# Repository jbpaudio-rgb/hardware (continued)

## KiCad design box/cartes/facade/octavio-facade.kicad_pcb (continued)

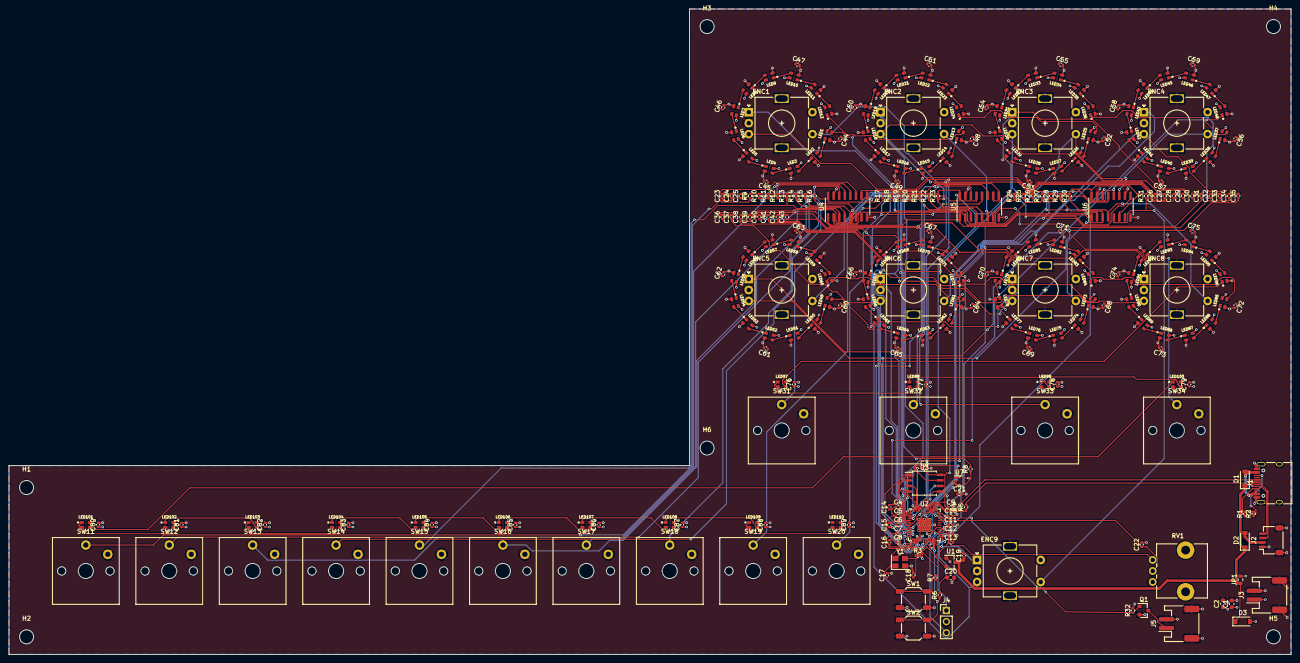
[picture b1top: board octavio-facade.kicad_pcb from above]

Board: 4 copper layers, 292.0 x 147.0 mm, 281 parts (0 on the bottom side), 187 nets.

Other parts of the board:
H1, H2, H3, H4, H5, H6: M3; MountingHole_3.2mm_M3

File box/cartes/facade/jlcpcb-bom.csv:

Comment,Designator,Footprint,LCSC Part #
TYPE-C-31-M-12,J1,USB_C_Receptacle_HRO_TYPE-C-31-M-12,C165948
5.1k,"R1,R2",R_0402_1005Metric,C25905
B5819W,"D1,D2,D3",D_SOD-123,C8598
SM04B-SRSS-TB,J2,JST_SH_SM04B-SRSS-TB_1x04-1MP_P1.00mm_Horizontal,C160404
S2B-PH-SM4-TB,"J3,J5",JST_PH_S2B-PH-SM4-TB_1x02-1MP_P2.00mm_Horizontal,C295747
10uF,"C1,C2,C20",C_0603_1608Metric,C19702
2N7002,Q1,SOT-23,C8545
100k,R32,R_0402_1005Metric,C25741
RP2040,U2,RP2040-QFN-56,C2040
W25Q16JVSSIQ,U3,SOIC-8_5.23x5.23mm_P1.27mm,C131025
100nF,"C3,C4,C5,C6,C7,C8,C9,C10,C11,C12,C13,C16,C21,C22,C23,C24,C25,C44,C45,C46,C47,C48,C49,C50,C51,C52,C53,C54,C55,C56,C57,C58,C59,C60,C61,C62,C63,C64,C65,C66,C67,C68,C69,C70,C71,C72,C73,C74,C75,C76,C77,C78,C79,C80,C81,C82,C83,C84,C85,C86,C87,C88,C89",C_0402_1005Metric,C1525
1uF,"C14,C15,C19",C_0402_1005Metric,C52923
X322512MSB4SI,Y1,Crystal_SMD_3225-4Pin_3.2x2.5mm,C9002
27pF,"C17,C18",C_0402_1005Metric,C1557
1k,"R3,R7",R_0402_1005Metric,C11702
27R,"R4,R5",R_0402_1005Metric,C25100
XC6206P332MR,U1,SOT-23,C5446
10k,"R6,R9,R10,R11,R12,R13,R14,R15,R16,R17,R18,R19,R20,R21,R22,R23,R24,R25,R26,R27,R28,R29,R30,R31",R_0402_1005Metric,C25744
TS-1187A-B-A-B,"SW1,SW2",SW_SPST_SKQG_WithoutStem,C318884
74AHCT1G125,U7,SOT-353_SC-70-5,C12495
330R,R8,R_0402_1005Metric,C25104
PEC11R-4220F-S0024,"ENC1,ENC2,ENC3,ENC4,ENC5,ENC6,ENC7,ENC8,ENC9",RotaryEncoder_Alps_EC11E-Switch_Vertical_H20mm,C143797
Kailh Choc CPG135001D01,"SW11,SW12,SW13,SW14,SW15,SW16,SW17,SW18,SW19,SW20,SW31,SW32,SW33,SW34",SW_Kailh_Choc_V1_1.00u,C400229
RK09L1140A2U 10k,RV1,Potentiometer_Alps_RK09L_Single_Vertical,C470448
74HC165D,"U4,U5,U6",SOIC-16_3.9x9.9mm_P1.27mm,C5613
10nF,"C26,C27,C28,C29,C30,C31,C32,C33,C34,C35,C36,C37,C38,C39,C40,C41,C42,C43",C_0402_1005Metric,C15195
WS2812B-2020,"LED1,LED2,LED3,LED4,LED5,LED6,LED7,LED8,LED9,LED10,LED11,LED12,LED13,LED14,LED15,LED16,LED17,LED18,LED19,LED20,LED21,LED22,LED23,LED24,LED25,LED26,LED27,LED28,LED29,LED30,LED31,LED32,LED33,LED34,LED35,LED36,LED37,LED38,LED39,LED40,LED41,LED42,LED43,LED44,LED45,LED46,LED47,LED48,LED49,LED50,LED51,LED52,LED53,LED54,LED55,LED56,LED57,LED58,LED59,LED60,LED61,LED62,LED63,LED64,LED65,LED66,LED67,LED68,LED69,LED70,LED71,LED72,LED73,LED74,LED75,LED76,LED77,LED78,LED79,LED80,LED81,LED82,LED83,LED84,LED85,LED86,LED87,LED88,LED89,LED90,LED91,LED92,LED93,LED94,LED95,LED96,LED97,LED98,LED99,LED100,LED101,LED102,LED103,LED104,LED105,LED106,LED107,LED108,LED109,LED110",LED_WS2812B-2020,C965555

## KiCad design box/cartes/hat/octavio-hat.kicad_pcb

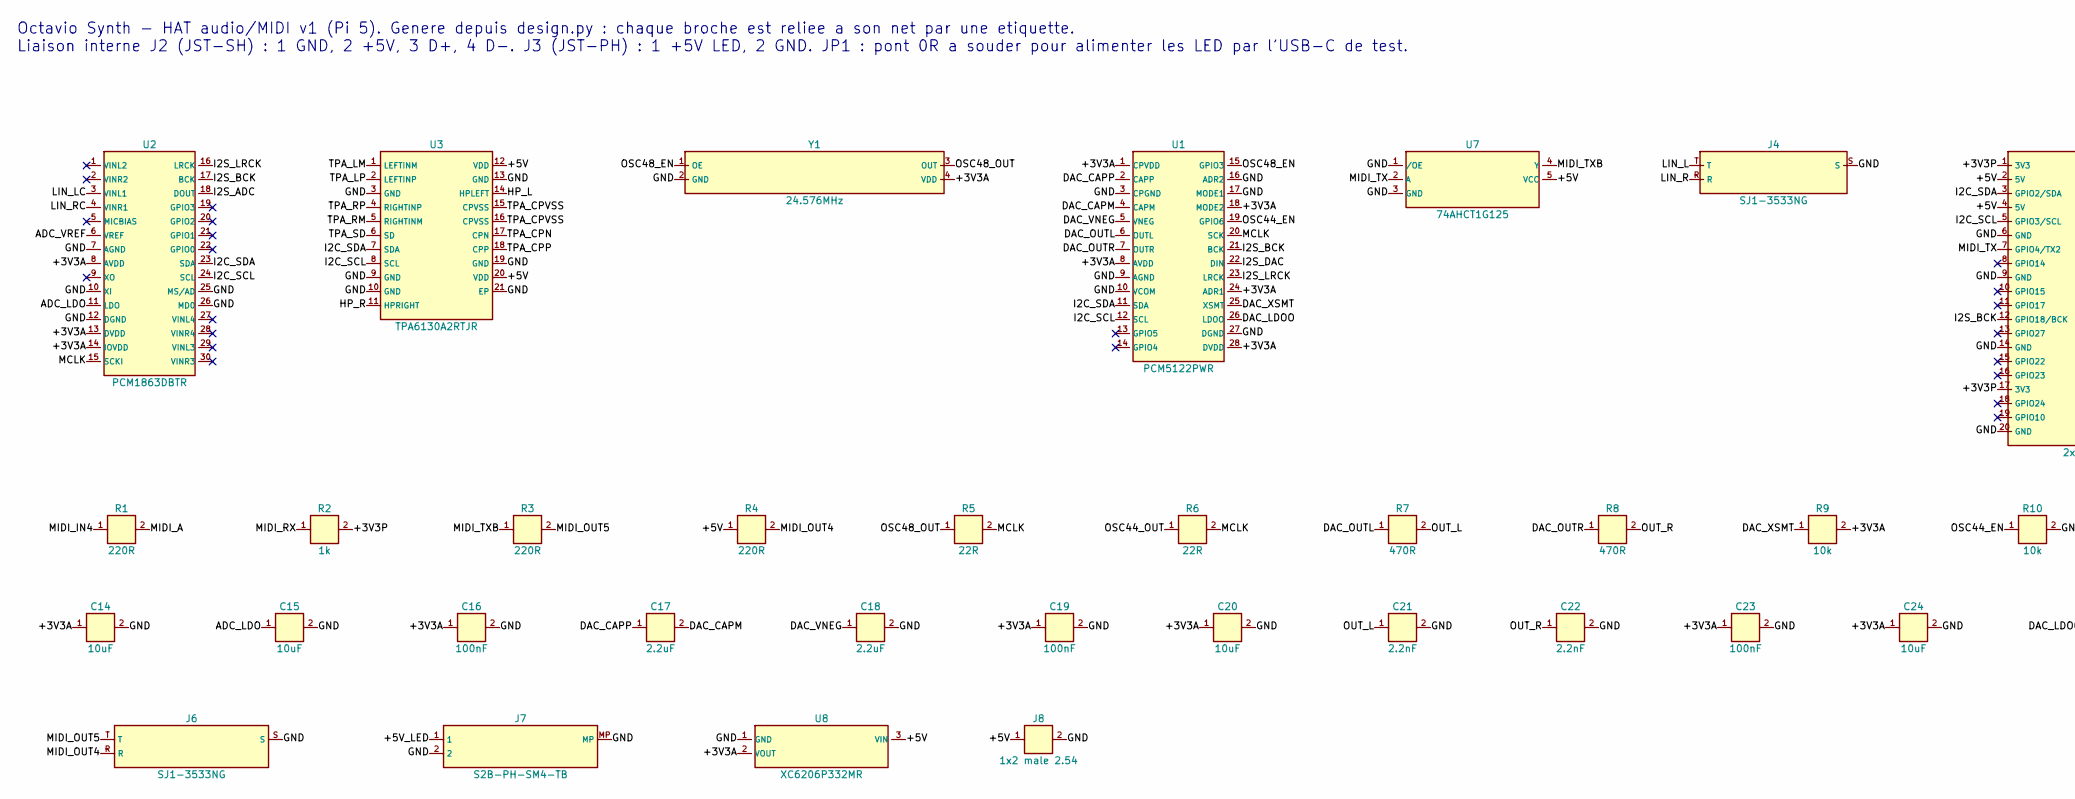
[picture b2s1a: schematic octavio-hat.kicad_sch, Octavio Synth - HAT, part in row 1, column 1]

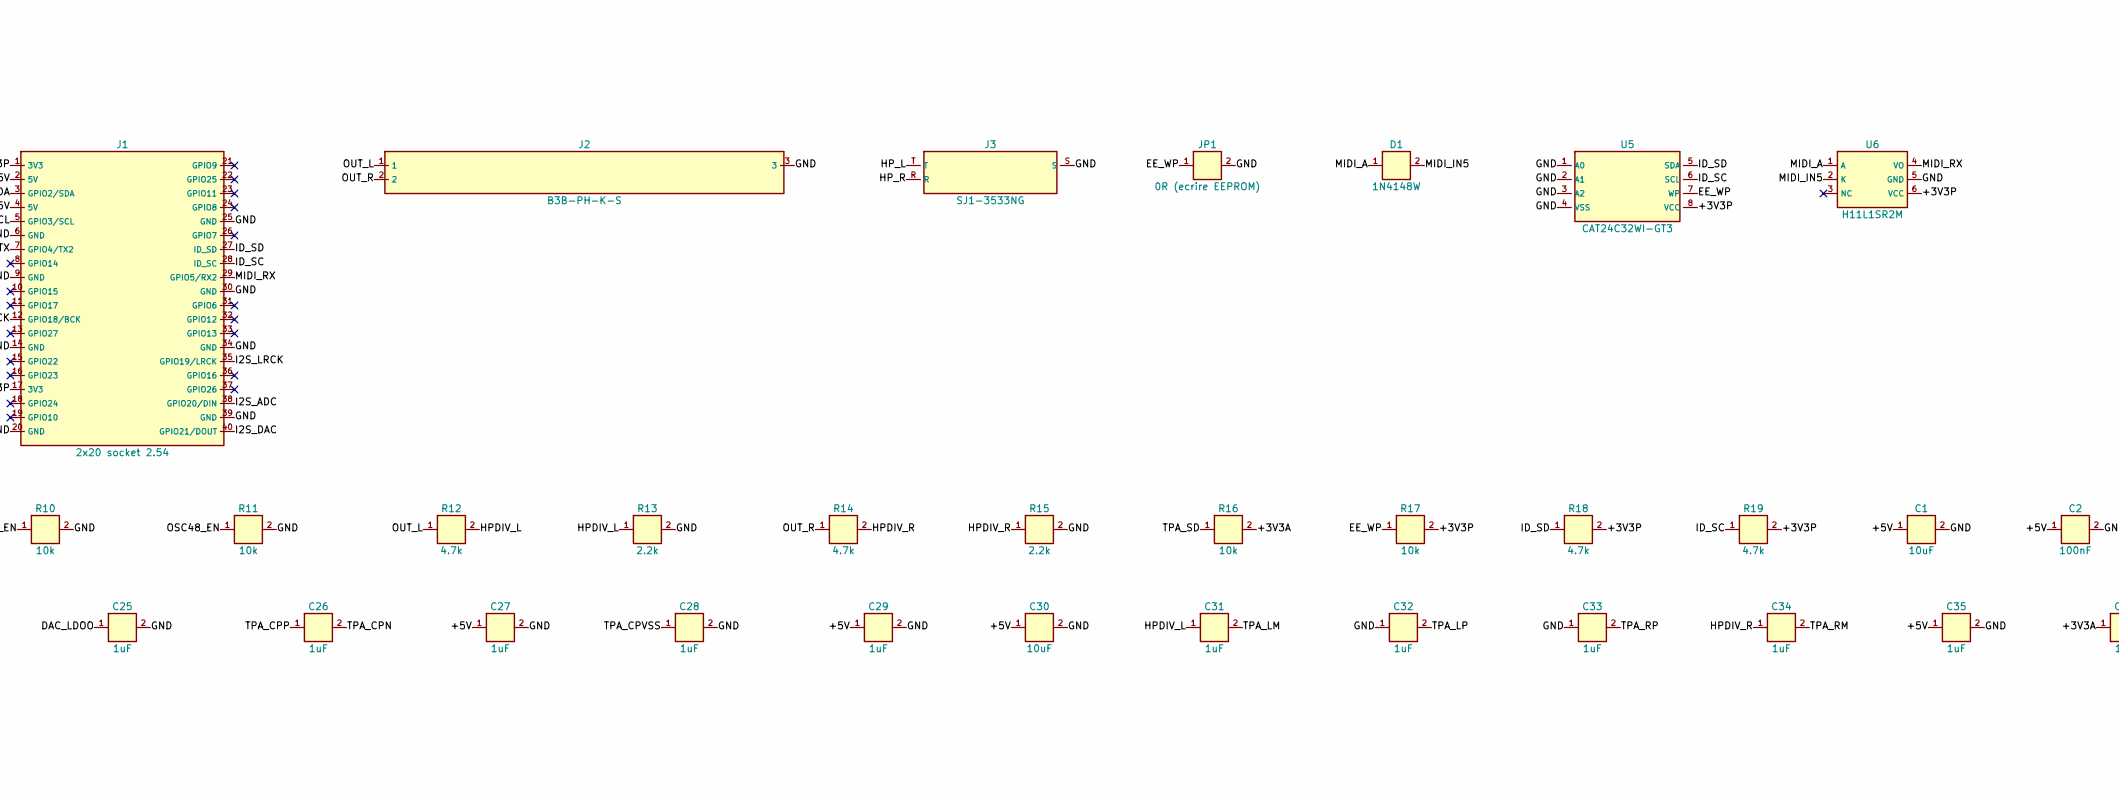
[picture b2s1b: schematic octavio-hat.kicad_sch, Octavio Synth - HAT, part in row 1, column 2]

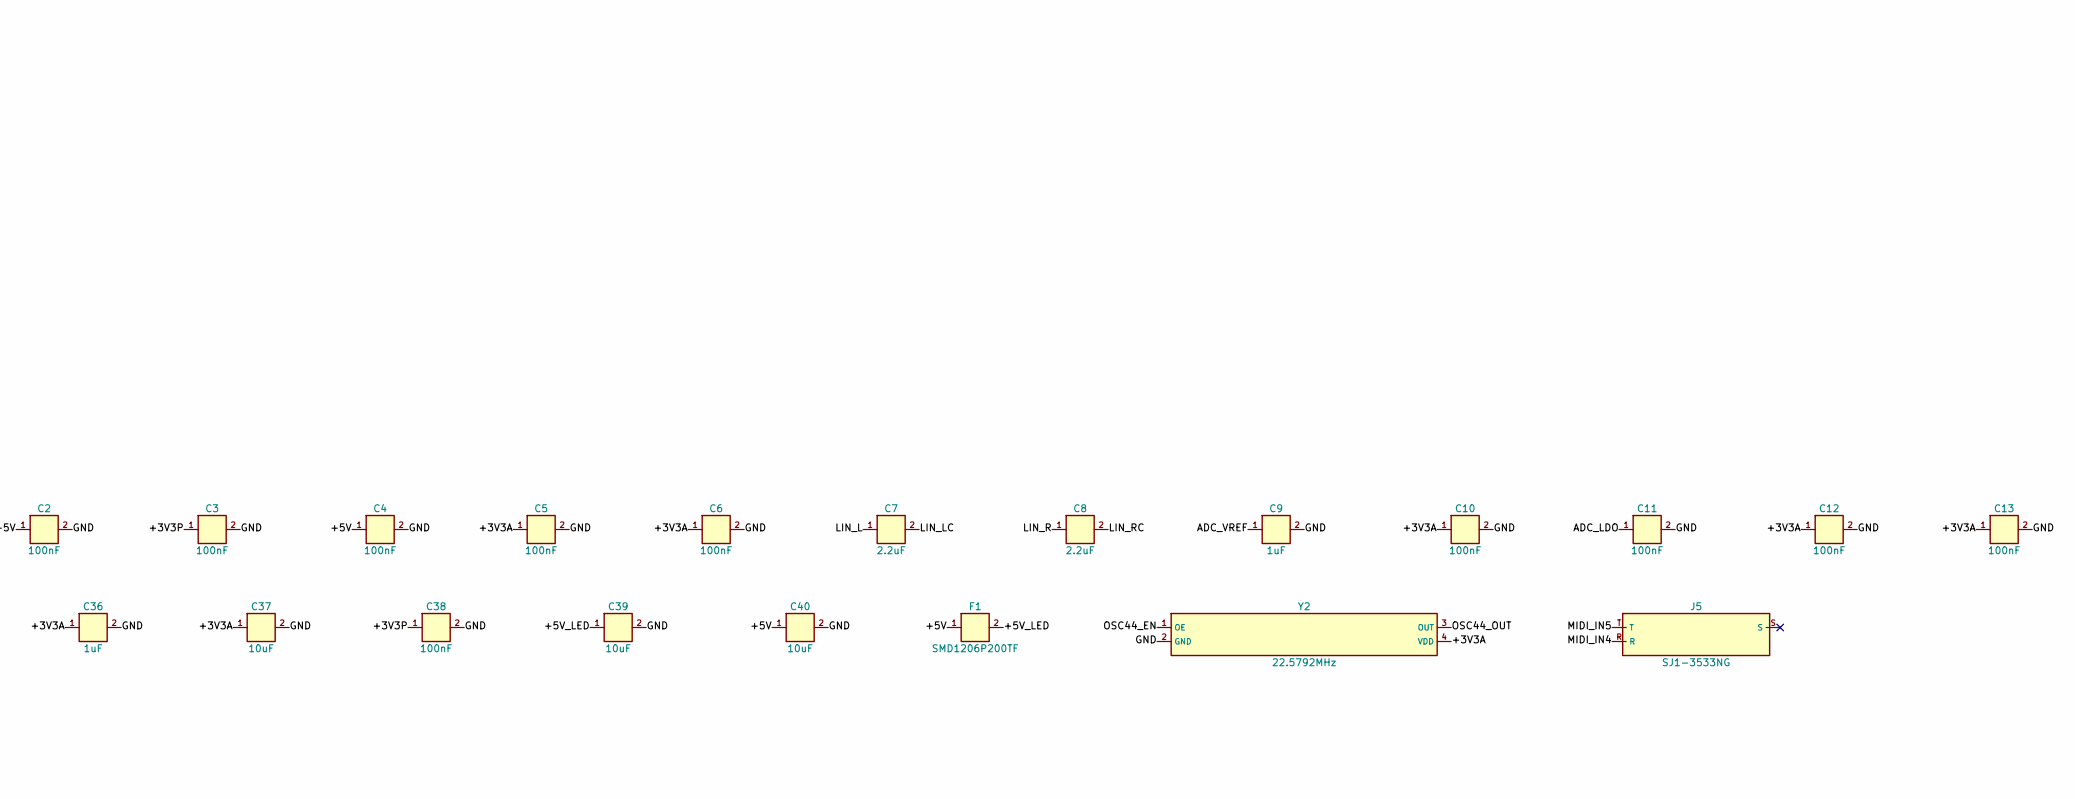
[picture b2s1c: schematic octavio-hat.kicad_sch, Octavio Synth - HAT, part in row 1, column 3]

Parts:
C1, C14, C15, C20, C24, C30, C37, C39, C40: 10uF; C_0603_1608Metric; LCSC C19702
C2, C3, C4, C5, C6, C10, C11, C12, C13, C16, C19, C23, C38: 100nF; C_0402_1005Metric; LCSC C1525
C7, C8, C17, C18: 2.2uF; C_0603_1608Metric; LCSC C23630
C9, C25, C26, C27, C28, C29, C31, C32, C33, C34, C35, C36: 1uF; C_0402_1005Metric; LCSC C52923
C21, C22: 2.2nF; C_0402_1005Metric; LCSC C1531
D1: 1N4148W; D_SOD-123; LCSC C81598
F1: SMD1206P200TF; Fuse_1206_3216Metric; LCSC C20988
J1: 2x20 socket 2.54; PinHeader_2x20_P2.54mm_Vertical; LCSC C2977589
J2: B3B-PH-K-S; JST_PH_B3B-PH-K_1x03_P2.00mm_Vertical; LCSC C131339
J3, J4, J5, J6: SJ1-3533NG; Jack_3.5mm_CUI_SJ1-3533NG_Horizontal; LCSC C4992459
J7: S2B-PH-SM4-TB; JST_PH_S2B-PH-SM4-TB_1x02-1MP_P2.00mm_Horizontal; LCSC C295747
J8: 1x2 male 2.54; PinHeader_1x02_P2.54mm_Vertical; LCSC C2905434
JP1: 0R (ecrire EEPROM); R_0402_1005Metric
R1, R3, R4: 220R; R_0402_1005Metric; LCSC C25091
R2: 1k; R_0402_1005Metric; LCSC C11702
R5, R6: 22R; R_0402_1005Metric; LCSC C25092
R7, R8: 470R; R_0402_1005Metric; LCSC C25117
R9, R10, R11, R16, R17: 10k; R_0402_1005Metric; LCSC C25744
R12, R14, R18, R19: 4.7k; R_0402_1005Metric; LCSC C25900
R13, R15: 2.2k; R_0402_1005Metric; LCSC C25879
U1: PCM5122PWR; TSSOP-28_4.4x9.7mm_P0.65mm; LCSC C962071
U2: PCM1863DBTR; TSSOP-30_4.4x7.8mm_P0.5mm; LCSC C529569
U3: TPA6130A2RTJR; QFN-20-1EP_4x4mm_P0.5mm_EP2.7x2.7mm_ThermalVias; LCSC C130046
U5: CAT24C32WI-GT3; SOIC-8_3.9x4.9mm_P1.27mm; LCSC C81193
U6: H11L1SR2M; SMDIP-6_W9.53mm; LCSC C20082
U7: 74AHCT1G125; SOT-353_SC-70-5; LCSC C12495
U8: XC6206P332MR; SOT-23; LCSC C5446
Y1: 24.576MHz; Oscillator_SMD_Abracon_ASE-4Pin_3.2x2.5mm; LCSC C437128
Y2: 22.5792MHz; Oscillator_SMD_Abracon_ASE-4Pin_3.2x2.5mm; LCSC C2901572

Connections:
+3V3A: C5.1, C6.1, C10.1, C12.1, C13.1, C14.1, C16.1, C19.1, C20.1, C23.1, C24.1, C36.1, C37.1, R9.2, R16.2, U1.1 (CPVDD), U1.8 (AVDD), U1.18 (MODE2), U1.24 (ADR1), U1.28 (DVDD), U2.8 (AVDD), U2.13 (DVDD), U2.14 (IOVDD), U8.2 (VOUT), Y1.4 (VDD), Y2.4 (VDD)
+3V3P: C3.1, C38.1, J1.1 (3V3), J1.17 (3V3), R2.2, R17.2, R18.2, R19.2, U5.8 (VCC), U6.6 (VCC)
+5V: C1.1, C2.1, C4.1, C27.1, C29.1, C30.1, C35.1, C40.1, F1.1, J1.2 (5V), J1.4 (5V), J8.1, R4.1, U3.12 (VDD), U3.20 (VDD), U7.5 (VCC), U8.3 (VIN)
+5V_LED: C39.1, F1.2, J7.1
ADC_LDO: C11.1, C15.1, U2.11 (LDO)
ADC_VREF: C9.1, U2.6 (VREF)
DAC_CAPM: C17.2, U1.4 (CAPM)
DAC_CAPP: C17.1, U1.2 (CAPP)
DAC_LDOO: C25.1, U1.26 (LDOO)
DAC_OUTL: R7.1, U1.6 (OUTL)
DAC_OUTR: R8.1, U1.7 (OUTR)
DAC_VNEG: C18.1, U1.5 (VNEG)
DAC_XSMT: R9.1, U1.25 (XSMT)
EE_WP: JP1.1, R17.1, U5.7 (WP)
GND: C1.2, C2.2, C3.2, C4.2, C5.2, C6.2, C9.2, C10.2, C11.2, C12.2, C13.2, C14.2, C15.2, C16.2, C18.2, C19.2, C20.2, C21.2, C22.2, C23.2, C24.2, C25.2, C27.2, C28.2, C29.2, C30.2, C32.1, C33.1, C35.2, C36.2, C37.2, C38.2, C39.2, C40.2, J1.6 (GND), J1.9 (GND), J1.14 (GND), J1.20 (GND), J1.25 (GND), J1.30 (GND), J1.34 (GND), J1.39 (GND), J2.3, J3.S, J4.S, J6.S, J7.2, J7.MP, J8.2, JP1.2, R10.2, R11.2, R13.2, R15.2, U1.3 (CPGND), U1.9 (AGND), U1.10 (VCOM), U1.16 (ADR2), U1.17 (MODE1), U1.27 (DGND), U2.7 (AGND), U2.10 (XI), U2.12 (DGND), U2.25 (MS/AD), U2.26 (MD0), U3.3 (GND), U3.9 (GND), U3.10 (GND), U3.13 (GND), U3.19 (GND), U3.21 (EP), U5.1 (A0), U5.2 (A1), U5.3 (A2), U5.4 (VSS), U6.5 (GND), U7.1 (/OE), U7.3 (GND), U8.1 (GND), Y1.2 (GND), Y2.2 (GND)
HPDIV_L: C31.1, R12.2, R13.1
HPDIV_R: C34.1, R14.2, R15.1
HP_L: J3.T, U3.14 (HPLEFT)
HP_R: J3.R, U3.11 (HPRIGHT)
I2C_SCL: J1.5 (GPIO3/SCL), U1.12 (SCL), U2.24 (SCL), U3.8 (SCL)
I2C_SDA: J1.3 (GPIO2/SDA), U1.11 (SDA), U2.23 (SDA), U3.7 (SDA)
I2S_ADC: J1.38 (GPIO20/DIN), U2.18 (DOUT)
I2S_BCK: J1.12 (GPIO18/BCK), U1.21 (BCK), U2.17 (BCK)
I2S_DAC: J1.40 (GPIO21/DOUT), U1.22 (DIN)
I2S_LRCK: J1.35 (GPIO19/LRCK), U1.23 (LRCK), U2.16 (LRCK)
ID_SC: J1.28 (ID_SC), R19.1, U5.6 (SCL)
ID_SD: J1.27 (ID_SD), R18.1, U5.5 (SDA)
LIN_L: C7.1, J4.T
LIN_LC: C7.2, U2.3 (VINL1)
LIN_R: C8.1, J4.R
LIN_RC: C8.2, U2.4 (VINR1)
MCLK: R5.2, R6.2, U1.20 (SCK), U2.15 (SCKI)
MIDI_A: D1.1, R1.2, U6.1 (A)
MIDI_IN4: J5.R, R1.1
MIDI_IN5: D1.2, J5.T, U6.2 (K)
MIDI_OUT4: J6.R, R4.2
MIDI_OUT5: J6.T, R3.2
MIDI_RX: J1.29 (GPIO5/RX2), R2.1, U6.4 (VO)
MIDI_TX: J1.7 (GPIO4/TX2), U7.2 (A)
MIDI_TXB: R3.1, U7.4 (Y)
OSC44_EN: R10.1, U1.19 (GPIO6), Y2.1 (OE)
OSC44_OUT: R6.1, Y2.3 (OUT)
OSC48_EN: R11.1, U1.15 (GPIO3), Y1.1 (OE)
OSC48_OUT: R5.1, Y1.3 (OUT)
OUT_L: C21.1, J2.1, R7.2, R12.1
OUT_R: C22.1, J2.2, R8.2, R14.1
TPA_CPN: C26.2, U3.17 (CPN)
TPA_CPP: C26.1, U3.18 (CPP)
TPA_CPVSS: C28.1, U3.15 (CPVSS), U3.16 (CPVSS)
TPA_LM: C31.2, U3.1 (LEFTINM)
TPA_LP: C32.2, U3.2 (LEFTINP)
TPA_RM: C34.2, U3.5 (RIGHTINM)
TPA_RP: C33.2, U3.4 (RIGHTINP)
TPA_SD: R16.1, U3.6 (SD)

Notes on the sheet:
Octavio Synth - HAT audio/MIDI v1 (Pi 5). Genere depuis design.py : chaque broche est reliee a son net par une etiquette. Liaison interne J2 (JST-SH) : 1 GND, 2 +5V, 3 D+, 4 D-. J3 (JST-PH) : 1 +5V LED, 2 GND. JP1 : pont 0R a souder pour alimenter les LED par l'USB-C de test.

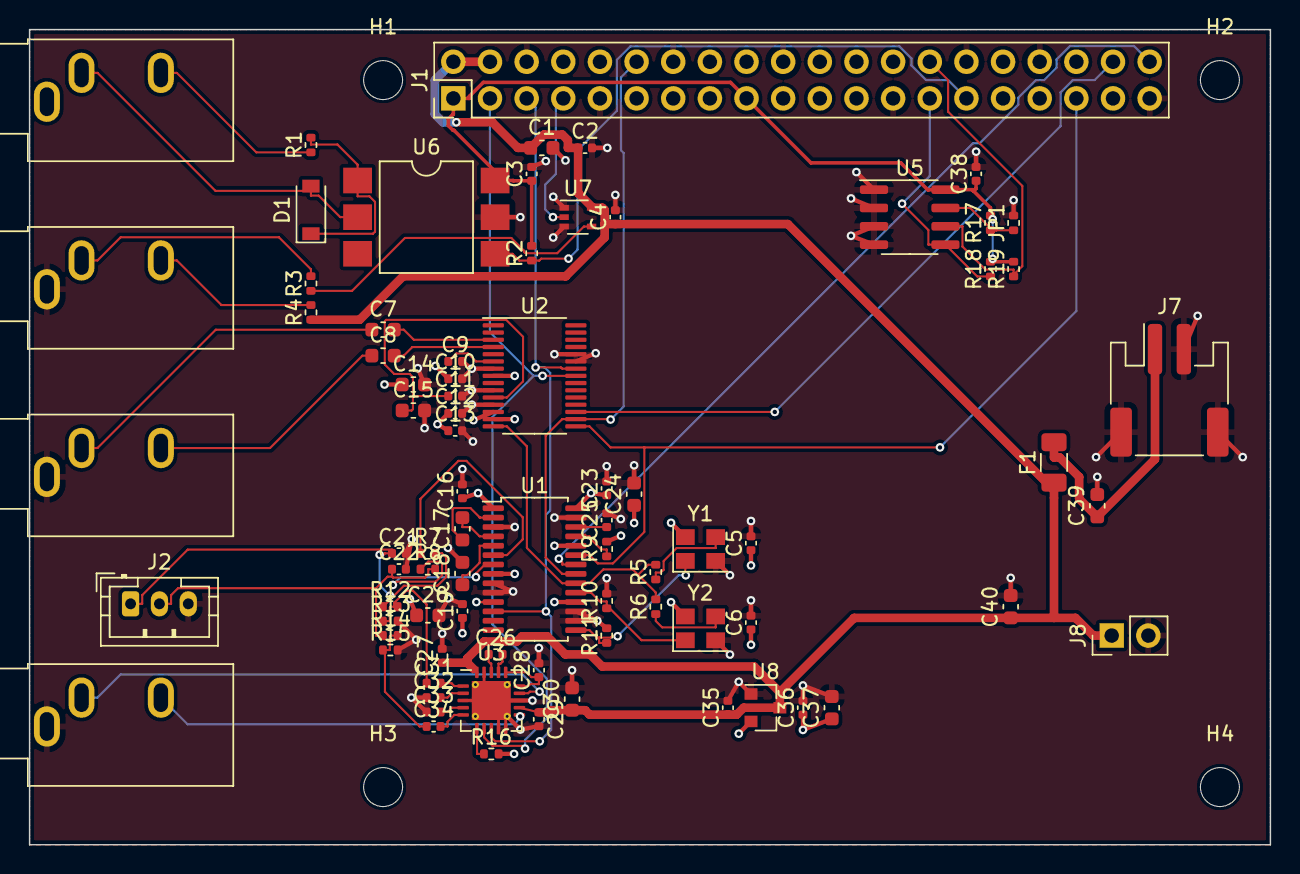
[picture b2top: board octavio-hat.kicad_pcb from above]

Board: 4 copper layers, 86.0 x 56.5 mm, 83 parts (0 on the bottom side), 54 nets.

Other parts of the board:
H1, H2, H3, H4: M2.5; MountingHole_2.7mm_M2.5

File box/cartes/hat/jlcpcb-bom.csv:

Comment,Designator,Footprint,LCSC Part #
2x20 socket 2.54,J1,PinHeader_2x20_P2.54mm_Vertical,C2977589
10uF,"C1,C14,C15,C20,C24,C30,C37,C39,C40",C_0603_1608Metric,C19702
100nF,"C2,C3,C4,C5,C6,C10,C11,C12,C13,C16,C19,C23,C38",C_0402_1005Metric,C1525
SJ1-3533NG,"J5,J6,J4,J3",Jack_3.5mm_CUI_SJ1-3533NG_Horizontal,C4992459
B3B-PH-K-S,J2,JST_PH_B3B-PH-K_1x03_P2.00mm_Vertical,C131339
220R,"R1,R3,R4",R_0402_1005Metric,C25091
1N4148W,D1,D_SOD-123,C81598
H11L1SR2M,U6,SMDIP-6_W9.53mm,C20082
1k,R2,R_0402_1005Metric,C11702
74AHCT1G125,U7,SOT-353_SC-70-5,C12495
24.576MHz,Y1,Oscillator_SMD_Abracon_ASE-4Pin_3.2x2.5mm,C437128
22.5792MHz,Y2,Oscillator_SMD_Abracon_ASE-4Pin_3.2x2.5mm,C2901572
22R,"R5,R6",R_0402_1005Metric,C25092
PCM1863DBTR,U2,TSSOP-30_4.4x7.8mm_P0.5mm,C529569
2.2uF,"C7,C8,C17,C18",C_0603_1608Metric,C23630
1uF,"C9,C25,C26,C27,C28,C29,C31,C32,C33,C34,C35,C36",C_0402_1005Metric,C52923
PCM5122PWR,U1,TSSOP-28_4.4x9.7mm_P0.65mm,C962071
470R,"R7,R8",R_0402_1005Metric,C25117
2.2nF,"C21,C22",C_0402_1005Metric,C1531
10k,"R9,R10,R11,R16,R17",R_0402_1005Metric,C25744
TPA6130A2RTJR,U3,QFN-20-1EP_4x4mm_P0.5mm_EP2.7x2.7mm_ThermalVias,C130046
4.7k,"R12,R14,R18,R19",R_0402_1005Metric,C25900
2.2k,"R13,R15",R_0402_1005Metric,C25879
XC6206P332MR,U8,SOT-23,C5446
CAT24C32WI-GT3,U5,SOIC-8_3.9x4.9mm_P1.27mm,C81193
SMD1206P200TF,F1,Fuse_1206_3216Metric,C20988
S2B-PH-SM4-TB,J7,JST_PH_S2B-PH-SM4-TB_1x02-1MP_P2.00mm_Horizontal,C295747
1x2 male 2.54,J8,PinHeader_1x02_P2.54mm_Vertical,C2905434

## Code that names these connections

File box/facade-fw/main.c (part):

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#define FW_MINOR 1

#define N_ENC 9
#define PIN_SR_CLK 18
#define PIN_SR_LD 19
#define PIN_SR_QH 20
#define PIN_LED 22
#define PIN_VOL 26
#define PIN_PWR 28        // -> Q1 (2N7002): pulls the Pi 5's power-button pads (its J2) low, to switch it on
#define ADC_VOL 0
#define N_LED 110
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static uint8_t btn_count[24];

static uint32_t sr_read(void) {
    gpio_put(PIN_SR_LD, 0);
    busy_wait_us_32(1);
    gpio_put(PIN_SR_LD, 1);
    busy_wait_us_32(1);
    uint32_t v = 0;
    for (int k = 0; k < 24; k++) {
        int input = 8 * (k / 8) + (7 - k % 8);
        if (gpio_get(PIN_SR_QH)) v |= 1u << input;
        gpio_put(PIN_SR_CLK, 1);
        busy_wait_us_32(1);
        gpio_put(PIN_SR_CLK, 0);
        busy_wait_us_32(1);
    }
    return v;
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        gpio_pull_up(p);                                     // encoder A/B (10 nF filter caps on the board)
    }
    gpio_init(PIN_PWR); gpio_set_dir(PIN_PWR, GPIO_OUT); gpio_put(PIN_PWR, 0);
    gpio_init(PIN_SR_CLK); gpio_set_dir(PIN_SR_CLK, GPIO_OUT); gpio_put(PIN_SR_CLK, 0);
    gpio_init(PIN_SR_LD); gpio_set_dir(PIN_SR_LD, GPIO_OUT); gpio_put(PIN_SR_LD, 1);
    gpio_init(PIN_SR_QH); gpio_set_dir(PIN_SR_QH, GPIO_IN);
    adc_init();
    adc_gpio_init(PIN_VOL);

    sleep_ms(5);
    uint32_t all = gpio_get_all();
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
